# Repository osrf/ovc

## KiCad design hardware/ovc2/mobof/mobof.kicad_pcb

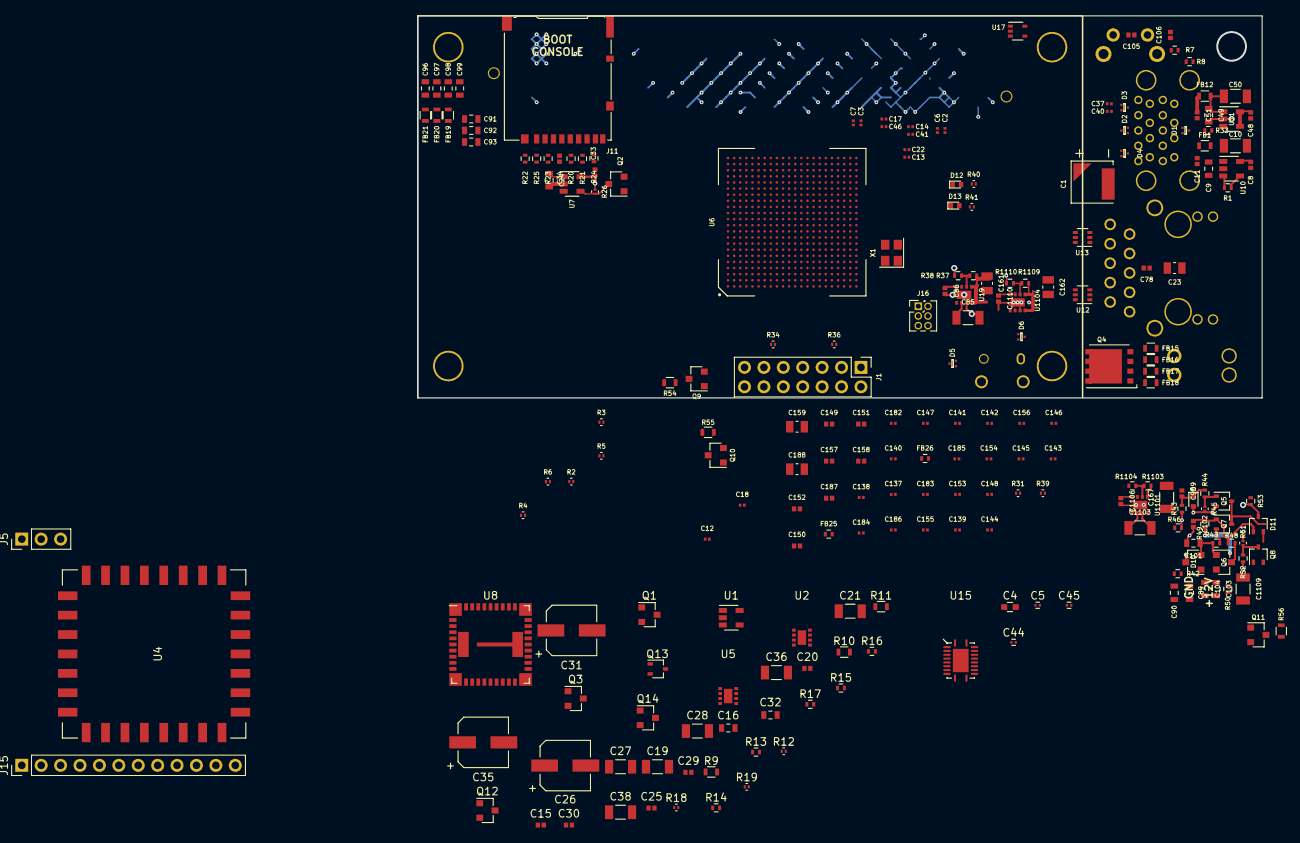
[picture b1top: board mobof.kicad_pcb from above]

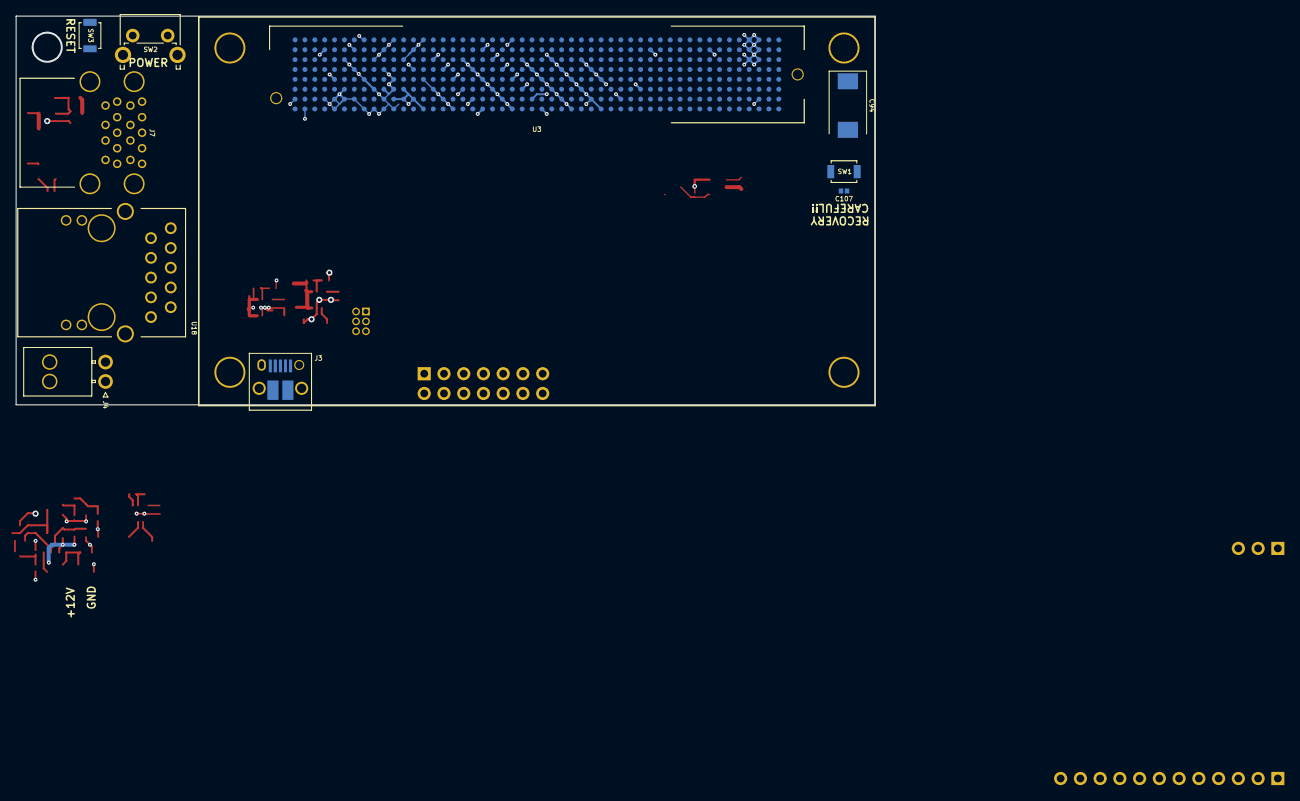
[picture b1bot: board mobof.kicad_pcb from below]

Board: 6 copper layers, 110.5 x 50.0 mm, 225 parts (10 on the bottom side), 154 nets.

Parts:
C1: 80m; SEIKO_XH414HG_IV01E
C2, C3, C6, C7, C12, C13, C14, C17, C22, C37, C40, C41, C46, C146, C147, C154, C155, C183, C184: 100n; C_0201_0603Metric
C4: 10u; C_0603
C5, C44, C45: 100n; C_0201
C8, C11, C30, C34, C48, C51: 100n; C_0402_1005Metric
C9, C24, C49, C91, C92, C93, C96, C97, C98, C99, C103, C104: 10u; C_0603_1608Metric
C10, C28, C36, C38, C50, C167: 100u; C_1206_3216Metric
C15, C33, C102, C150, C158, C187: 1u; C_0402_1005Metric
C16, C101: 2u2; C_0603_1608Metric
C18, C143: 10n; C_0201_0603Metric
C19, C21, C27, C85, C1103, C1109: 47u; C_1206_3216Metric
C20, C25, C86, C1106, C1110: 4n7; C_0402_1005Metric
C23: 100p; C_0805_2012Metric
C26: 100u; CP_Elec_6.3x7.7
C29, C78: 10n; C_0402_1005Metric
C31, C35: 220u; CP_Elec_6.3x5.8
C32: 22u; C_0603_1608Metric
C89: 100n; C_0603_1608Metric
C90: 4u7; C_0603_1608Metric
C94: 100u; CP_EIA-7343-43_Kemet-X
C95, C149, C157: 470n; C_0402_1005Metric
C105, C106, C107: 1n; C_0402_1005Metric
C137, C138, C139, C140, C141, C142, C153, C182: 22n; C_0201_0603Metric
C144, C145: 47n; C_0201_0603Metric
C148, C156, C185: 220n; C_0201_0603Metric
C151, C152: 4u7; C_0402_1005Metric
C159, C188: 100u; C_0805_2012Metric
C161, C162: 22u; C_0805_2012Metric
C186: 470n; C_0201_0603Metric
D1, D2, D3, D4, D5, D6: TPD2EUSB30A; TPD2EUSB30x
D9: RB521S30T1G; D_SOD-523
D10: BAT54ALT1G; SOT-23
D11: BAT54CW-7-F; SOT-323_SC-70
D12: LED_Red; LED_0402
D13: LED_Green; LED_0402
FB1, FB12: 220; R_0603
FB15, FB16, FB17, FB18, FB19, FB20, FB21: 30; R_0603
FB25, FB26: 60; R_0402
J1: FPGA DEBUG; Pin_Header_Straight_2x07_Pitch2.54mm
J3: USB_OTG; USB_Micro-B_10103594-0001LF
J4: POWER; Molex_NanoFit_1x02x2.50mm_Angled
J5: IMU DEBUG; Pin_Header_Straight_1x03_Pitch2.54mm
J7: USB3_A_STACKED; MOLEX_0484060003
J11: Micro_SD_Card_Det_Hirose_DM3AT; Hirose_DM3AT-SF-PEJM5
J15: IMU; Pin_Header_Straight_1x12_Pitch2.54mm
J16: FPGA CONFIG; Pin_Header_Straight_2x03_Pitch1.27mm
Q1, Q3, Q9, Q10, Q11, Q12: NTR4003NT1G; SOT-23
Q2, Q14: DMN2041L; SOT-23
Q4: AON6407; TDSON-8-1
Q5, Q7, Q8, Q13: NTS4001NT1G; SOT-323_SC-70
Q6: MMBT4403; SOT-23
R1, R33, R42, R44, R46, R47, R48: 10k; R_0402
R2, R3, R4, R5, R6, R12: 10k; R_0201
R7, R8: 681; R_0402
R9, R10, R11, R56: 47; R_0603
R13: 124k; R_0402
R14, R15, R17, R38, R43, R49, R52, R53, R1104, R1110: 100k; R_0402
R16: 28k7; R_0402
R18: 1M; R_0201
R19: 2k87; R_0201
R20: 0; R_0402
R21, R22, R23, R24, R25: 10; R_0402
R26, R45, R51: 47k; R_0201
R31, R39: 2k; R_0201
R34, R36: 1k; R_0201
R37, R1109: 523k; R_0402
R40, R41: 330; R_0201
R50: 10M; R_0402
R54, R55: 100; R_0603
R1103: 316k; R_0402
SW1: recovery; SW_SPST_B3U-1000P
SW2: SW_Push; SW_Tactile_SPST_Angled_PTS645Vx58-2LFS
SW3: SW_Push; SW_SPST_B3U-1000P
U1: TPS70933DBV; SOT-23-5
U2, U5, U19, U1101, U1104: TPS82130
U3: Jetson; JETSON_TX
U4: VN-100
U6: 10CX220; INTEL_U484
U7: NCP380LSN10AAT1G; SOT-23-5
U8: LMZ31707; TI_RVQ_42
U10, U11: TPS2069C; SOT-23-5
U12, U13: SP3002-04JTG; SOT-363_SC-70-6
U15: TXB0108RGY; TI_VQFN_20_RGY
U17: 74LVC1G34; SOT-353_SC-70-5
U18: ARJ11C-MBSAS-A-BA-7MU2
X1: ASEMB-100MHz; Oscillator_SMD_Abracon_ASE-4pin_3.2x2.5mm

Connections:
0V9: C35.1, C36.1, C38.1, C137.1, C138.1, C139.1, C140.1, C141.1, C142.1, C143.1, C144.1, C145.1, C146.1, C147.1, C148.1, C149.1, C150.1, C151.1, C152.1, R10.1, U6.J12, U6.J13, U6.K6, U6.K12, U6.K14, U6.K15, U6.K16, U6.L6, U6.L7, U6.L8, U6.L9, U6.L11, U6.L12, U6.L13, U6.L14, U6.L16, U6.M6, U6.M10, U6.M14, U6.M15, U6.M16, U6.N6, U6.N7, U6.N8, U6.N10, U6.N11, U6.N12, U6.N13, U6.N15, U6.N16, U6.P7, U6.P8, U6.P9, U6.P10, U6.P12, U6.P13, U6.P14, U6.P15, U6.R6, U6.R7, U6.R11, U6.R12, U6.R15, U6.R16, U8.27, U8.34, U8.35, U8.36, U8.37, U8.38, U8.41
1V03: C32.1, FB26.2, R11.1, R16.1, U5.4, U5.5
3V3_ALWAYS_ON: C16.1, R12.1, R15.2, U1.5
+1V8: C12.1, C18.1, C28.1, C31.1, C44.1, FB25.2, J1.9, R2.1, R3.1, R4.1, R5.1, R6.1, R9.1, R13.1, R34.1, U2.4, U2.5, U6.C9, U6.D11, U6.D16, U6.F10, U6.F15, U6.H14, U6.J1, U6.J8, U6.J14, U6.K2, U6.K3, U6.R9, U6.R14, U6.T8, U6.T9, U6.T15, U6.U9, U6.U12, U6.V9, U6.V14, U6.W6, U6.Y8, U15.2, U15.10, U17.5, X1.1, X1.4
+3V3: C4.1, C5.1, C33.1, C45.1, C167.1, J15.1, R26.1, R56.1, R1103.1, U4.10, U7.5, U15.19, U18.12, U18.13, U1101.4, U1101.5
+5V: C8.1, C162.1, R55.1, R1109.1, U10.5, U1104.4, U1104.5
+12V: C15.1, C19.1, C21.1, C26.1, C27.1, C30.1, C85.1, C91.1, C92.1, C93.1, C95.1, C1103.1, C1109.1, D10.3, FB19.2, FB20.2, FB21.2, Q4.5, R46.1, R51.1, U1.1, U2.2, U5.2, U8.1, U8.3, U8.11, U8.12, U8.39, U8.40, U19.2, U1101.2, U1104.2
/fpga_config/TCK: J1.3, R36.1, U6.P5
/fpga_config/TDI: J1.7, R4.2, U6.M4
/fpga_config/TDO: J1.1, U6.M5
/fpga_config/TMS: J1.5, R6.2, U6.L3
/fpga_io/CLK100: U6.AA6, X1.3
/fpga_io/PCIE_RST_1V8: U6.AB8, U17.4
/fpga_pcie/GXB_TX_L0+: C22.2, U6.AA22
/fpga_pcie/GXB_TX_L0-: C13.2, U6.AA21
/fpga_pcie/GXB_TX_L1+: C14.2, U6.W22
/fpga_pcie/GXB_TX_L1-: C41.2, U6.W21
/fpga_pcie/REFCLK+: C17.2, U6.M20
/fpga_pcie/REFCLK-: C46.2, U6.M19
/fpga_power/RREF_BL: R31.1, U6.AB19
/fpga_power/RREF_TL: R39.1, U6.A22
/fpga_power/VCCA: C182.1, C183.1, C184.1, C185.1, C186.1, C187.1, C188.1, FB25.1, U6.L19, U6.M11, U6.M13
/fpga_power/VCC_GXBL: C153.1, C154.1, C155.1, C156.1, C157.1, C158.1, C159.1, FB26.1, U6.J19, U6.J20, U6.N19, U6.N20
/imu/CS_3V3: J15.12, U4.23, U15.12
/imu/MISO_3V3: J15.9, U4.19, U15.15
/imu/MOSI_3V3: J15.8, U4.17, U15.16
/imu/NRST_3V3: J15.10, U4.21, U15.14
/imu/RX2: J5.1, U4.6
/imu/SCK_3V3: J15.7, U4.16, U15.17
/imu/SYNC_IN_3V3: J15.11, U4.22, U15.13
/imu/SYNC_OUT_3V3: J15.4, U4.9, U15.18
/imu/TARE_3V3: J15.3, U4.7, U15.20
/imu/TX2: J5.2, U4.5
/jetson_enet/GBE_MDI0+: U3.E48, U12.1, U18.1
/jetson_enet/GBE_MDI0-: U3.E49, U12.3, U18.2
/jetson_enet/GBE_MDI1+: U3.F47, U12.6, U18.3
/jetson_enet/GBE_MDI1-: U3.F48, U12.4, U18.4
/jetson_enet/GBE_MDI2+: U3.G48, U13.1, U18.7
/jetson_enet/GBE_MDI2-: U3.G49, U13.3, U18.8
/jetson_enet/GBE_MDI3+: U3.H47, U13.6, U18.9
/jetson_enet/GBE_MDI3-: U3.H48, U13.4, U18.10
/jetson_enet/LINK_1G: R8.1, U18.11
/jetson_enet/LINK_ACT: R7.1, U18.14
/jetson_pcie/PEX0_TX+: C6.2, U3.E44
/jetson_pcie/PEX0_TX-: C2.2, U3.E45
/jetson_pcie/PEX1_TX+: C7.2, U3.D42
/jetson_pcie/PEX1_TX-: C3.2, U3.D43
/jetson_power/POWER_BTN: C105.1, SW2.1, U3.B50
/jetson_power/RESET_IN: C106.1, SW3.1, U3.A47
/jetson_power/VDD_RTC: C1.1, U3.A50
/jetson_sdcard/SDCARD_CD: J11.9, U3.F17
/jetson_sdcard/SDCARD_CLK: J11.5, R20.1
/jetson_sdcard/SDCARD_CMD: J11.3, R23.1
/jetson_sdcard/SDCARD_D0: J11.7, R21.1
/jetson_sdcard/SDCARD_D1: J11.8, R24.1
/jetson_sdcard/SDCARD_D2: J11.1, R22.1
/jetson_sdcard/SDCARD_D3: J11.2, R25.1
/jetson_sdcard/SDCARD_PWR_EN: Q2.1, U3.H16
/jetson_sdcard/SDCARD_VDD: C24.1, C34.1, J11.4, U7.1
/jetson_usb/SS1_TX+: C37.2, U3.C43
/jetson_usb/SS1_TX-: C40.2, U3.C44
/jetson_usb/USB1_D+: D1.1, J7.3, U3.A38
/jetson_usb/USB1_D-: D1.2, J7.2, U3.A39
/jetson_usb/USB1_EN: R1.1, U3.A18, U10.4
/jetson_usb/USB1_VBUS: C11.1, FB1.2, J7.1
/power/AGND: C29.2, Q14.2, R18.2, R19.2, U8.2, U8.23, U8.29
/power/DROP_DETECT: C102.1, D11.1, Q7.1, R48.2, R49.1
/power/PG_GRP1: R15.1, U2.1, U8.8
/power/PH: U8.10, U8.13, U8.14, U8.15, U8.16, U8.17, U8.18, U8.19, U8.42
/power/VIN: FB15.2, FB16.2, FB17.2, FB18.2, J4.1
/power/~PWR_EN: D11.2, Q8.3, R51.2, R52.1
/power/~PWR_EN_GRP1: Q13.3, Q14.1, R12.2
DISCHARGE: D11.3, Q1.1, Q3.1, Q9.1, Q10.1, Q11.1, Q12.1, R53.1
FPGA_CONFIG_DATA0: J16.3, U3.F13, U6.V7
FPGA_CONFIG_DCLK: J16.4, U3.G13, U6.T2
FPGA_CONF_DONE: J16.1, R3.2, U6.M1
FPGA_NCONFIG: J16.5, R2.2, U6.U5
FPGA_NSTATUS: J16.2, R5.2, U6.L1
GND: C1.2, C4.2, C5.2, C8.2, C9.2, C10.2, C11.2, C12.2, C15.2, C16.2, C18.2, C19.2, C20.2, C21.2, C23.2, C24.2, C25.2, C26.2, C27.2, C28.2, C30.2, C31.2, C32.2, C33.2, C34.2, C35.2, C36.2, C38.2, C44.2, C45.2, C48.2, C49.2, C50.2, C51.2, C78.1, C85.2, C86.2, C89.2, C91.2, C92.2, C93.2, C94.2, C96.2, C97.2, C98.2, C99.2, C101.2, C102.2, C103.2, C104.2, C105.2, C106.2, C107.2, C137.2, C138.2, C139.2, C140.2, C141.2, C142.2, C143.2, C144.2, C145.2, C146.2, C147.2, C148.2, C149.2, C150.2, C151.2, C152.2, C153.2, C154.2, C155.2, C156.2, C157.2, C158.2, C159.2, C161.2, C162.2, C167.2, C182.2, C183.2, C184.2, C185.2, C186.2, C187.2, C188.2, C1103.2, C1106.2, C1109.2, C1110.2, D1.3, D2.3, D3.3, D4.3, D5.3, D6.3, D9.2, D12.1, D13.1, J1.13, J3.5, J3.6, J4.2, J5.3, J7.4, J7.7, J7.13, J7.16, J11.6, J11.10, J11.11, J15.2, J16.6, Q1.2, Q2.2, Q3.2, Q5.2, Q7.2, Q8.2, Q9.2, Q10.2, Q11.2, Q12.2, Q13.2, R14.2, R17.2, R31.2, R36.2, R38.2, R39.2, R42.2, R43.2, R45.2, R46.2, R47.2, R49.2, R50.2, R52.2, R53.2, R1104.2, R1110.2, SW1.2, SW2.2, SW3.2, U1.2, U2.3, U2.9, U3.A3, U3.A4, U3.A28, U3.A37, U3.A40, U3.A43, U3.B3, U3.B4, U3.B14, U3.B31, U3.B38, U3.B41, U3.B44, U3.B47, U3.C3, U3.C4, U3.C21, U3.C24, U3.C27, U3.C30, U3.C33, U3.C36, U3.C39, U3.C42, U3.C45, U3.D20, U3.D23, U3.D26, U3.D29, U3.D32, U3.D35, U3.D38, U3.D41, U3.D44, U3.E19, U3.E22, U3.E25, U3.E28, U3.E31, U3.E34, U3.E37, U3.E40, U3.E43, U3.E46, U3.F10, U3.F15, U3.F21, U3.F24, U3.F27, U3.F30, U3.F33, U3.F36, U3.F39, U3.F40, U3.F41, U3.F42, U3.F45, U3.F49, U3.G3, U3.G17, U3.G20, U3.G23, U3.G26, U3.G29, U3.G32, U3.G35, U3.G38, U3.G39, U3.G40, U3.G41, U3.G44, U3.G45, U3.G46, U3.G47, U3.G50, U3.H19, U3.H22, U3.H25, U3.H28, U3.H31, U3.H34, U3.H37, U3.H40, U3.H41, U3.H42, U3.H43, U3.H46, U3.H49, U4.1, U4.2, U4.3, U4.4, U4.18, U4.28, U4.30, U5.3, U5.9, U6.A4, U6.A9, U6.A14, U6.A18, U6.A19, U6.A20, U6.A21, U6.AA5, U6.AA10, U6.AA15, U6.AA18, U6.AA19, U6.AA20, U6.AB2, U6.AB7, U6.AB12, U6.AB20, U6.AB21, U6.AB22, U6.B2, U6.B7, U6.B12, U6.B17, U6.B18, U6.B19, U6.B20, U6.B21, U6.B22, U6.C4, U6.C14, U6.C20, U6.D1, U6.D4, U6.D5, U6.D6, U6.D18, U6.D20, U6.D21, U6.D22, U6.E3, U6.E4, U6.E5, U6.E6, U6.E8, U6.E13, U6.E20, U6.E21, U6.E22, U6.F3, U6.F4, U6.F5, U6.F7, U6.F12, U6.F20, U6.F21, U6.F22, U6.G2, U6.G3, U6.G7, U6.G9, U6.G10, U6.G12, U6.G17, U6.G20, U6.H2, U6.H4, U6.H9, U6.H10, U6.H18, U6.H19, U6.H20, U6.H21, U6.H22, U6.J6, U6.J9, U6.J10, U6.J11, U6.J15, U6.J16, U6.J18, U6.J21, U6.J22, U6.K8, U6.K9, U6.K10, U6.K11, U6.K13, U6.K18, U6.K19, U6.K20, U6.K21, U6.K22, U6.L5, U6.L10, U6.L15, U6.L18, U6.L20, U6.M2, U6.M3, U6.M7, U6.M12, U6.M18, U6.M21, U6.M22, U6.N3, U6.N4, U6.N5, U6.N9, U6.N14, U6.N18, U6.N21, U6.N22, U6.P1, U6.P3, U6.P6, U6.P11, U6.P16, U6.P18, U6.P19, U6.P20, U6.P21, U6.P22, U6.R3, U6.R5, U6.R8, U6.R13, U6.R20, U6.T3, U6.T5, U6.T7, U6.T10, U6.T11, U6.T13, U6.T20, U6.T21, U6.T22, U6.U2, U6.U4, U6.U7, U6.U17, U6.U20, U6.V4, U6.V20, U6.V21, U6.V22, U6.W1, U6.W9, U6.W11, U6.W16, U6.W18, U6.W19, U6.W20, U6.Y3, U6.Y13, U6.Y18, U6.Y21, U6.Y22, U7.2, U8.20, U8.21, U8.31, U8.32, U8.33, U10.2, U11.2, U12.2, U13.2, U15.11, U15.21, U17.3, U19.3, U19.9, U1101.3, U1101.9, U1104.3, U1104.9, X1.2
IMU_RX1: J15.6, U4.13
IMU_TX1: J15.5, U4.12
JETSON_CARRIER_PWR_ON: Q8.1, Q13.1, U3.A48, U5.1, U19.1, U1101.1, U1104.1
JETSON_PWR_BAD: Q5.3, Q7.3, U3.B8
JETSON_RESET_OUT: U2.7, U3.A46
JETSON_VDD_MOD: C94.1, C96.1, C97.1, C98.1, C99.1, FB19.1, FB20.1, FB21.1, U3.A1, U3.A2, U3.B1, U3.B2, U3.C1, U3.C2
unnamed: C9.1, C10.1, FB1.1, U10.1
unnamed: C20.1, U2.8
unnamed: C23.1, U18.SHLD
unnamed: C25.1, U5.8
unnamed: C29.1, U8.28
unnamed: C49.1, C50.1, FB12.1, U11.1
unnamed: C78.2, U18.5, U18.6
unnamed: C86.1, U19.8
unnamed: C89.1, C90.1, FB15.1, FB16.1, FB17.1, FB18.1, Q4.1, Q4.2, Q4.3
unnamed: C90.2, Q4.4, R42.1
unnamed: C95.2, D9.1, R43.1, R44.1
unnamed: C101.1, D10.2, Q6.1, R47.1
unnamed: C103.1, C104.1, D10.1, Q6.2, R50.1
unnamed: C107.1, SW1.1, U3.E1
unnamed: C1106.1, U1101.8
unnamed: C1110.1, U1104.8
unnamed: D12.2, R40.1
unnamed: D13.2, R41.1
unnamed: Q1.3, R9.2
unnamed: Q2.3, R26.2, U7.4
unnamed: Q3.3, R10.2
unnamed: Q5.1, R44.2, R45.1
unnamed: Q6.3, R48.1
unnamed: Q9.3, R54.2
unnamed: Q10.3, R55.2
unnamed: Q11.3, R56.2
unnamed: Q12.3, R11.2
unnamed: Q14.3, U8.30
unnamed: R1.2, U10.3
unnamed: R7.2, U3.E47
unnamed: R8.2, U3.F46
unnamed: R13.2, R14.1, U2.6
unnamed: R16.2, R17.1, U5.6
unnamed: R18.1, U8.22
unnamed: R19.1, U8.26
unnamed: R20.2, U3.G18
unnamed: R21.2, U3.H18
unnamed: R22.2, U3.F19
unnamed: R23.2, U3.G19
unnamed: R24.2, U3.H17
unnamed: R25.2, U3.F18
unnamed: R33.2, U11.3
unnamed: R34.2, U6.L4
unnamed: R37.2, R38.1, U19.6
unnamed: R1103.2, R1104.1, U1101.6
unnamed: R1109.2, R1110.1, U1104.6
PCIE_LANE0_RX+: C22.1, U3.H44
PCIE_LANE0_RX-: C13.1, U3.H45
PCIE_LANE0_TX+: C6.1, U6.Y20
PCIE_LANE0_TX-: C2.1, U6.Y19
PCIE_LANE1_RX+: C14.1, U3.G42
PCIE_LANE1_RX-: C41.1, U3.G43
PCIE_LANE1_TX+: C7.1, U6.U22
PCIE_LANE1_TX-: C3.1, U6.U21
PCIE_REFCLK+: C17.1, U3.A44
PCIE_REFCLK-: C46.1, U3.A45
PCIE_RST_3V3: U3.C49, U17.2
USB0_D+: D5.2, J3.3, U3.B39
USB0_D-: D5.1, J3.2, U3.B40
USB0_ID: D6.2, J3.4, U3.A36
USB0_VBUS: J3.1, U3.B37
USB1_SSRX+: D4.1, J7.15, U3.F43
USB1_SSRX-: D4.2, J7.14, U3.F44
USB1_SSTX+: C37.1, D3.1, J7.18
USB1_SSTX-: C40.1, D3.2, J7.17
USB2_5V: C48.1, C161.1, R33.1, R37.1, R54.1, U11.4, U11.5, U19.4, U19.5
USB2_5V_LIM: C51.1, FB12.2, J7.10
USB2_D+: D2.1, J7.12, U3.B42
USB2_D-: D2.2, J7.11, U3.B43

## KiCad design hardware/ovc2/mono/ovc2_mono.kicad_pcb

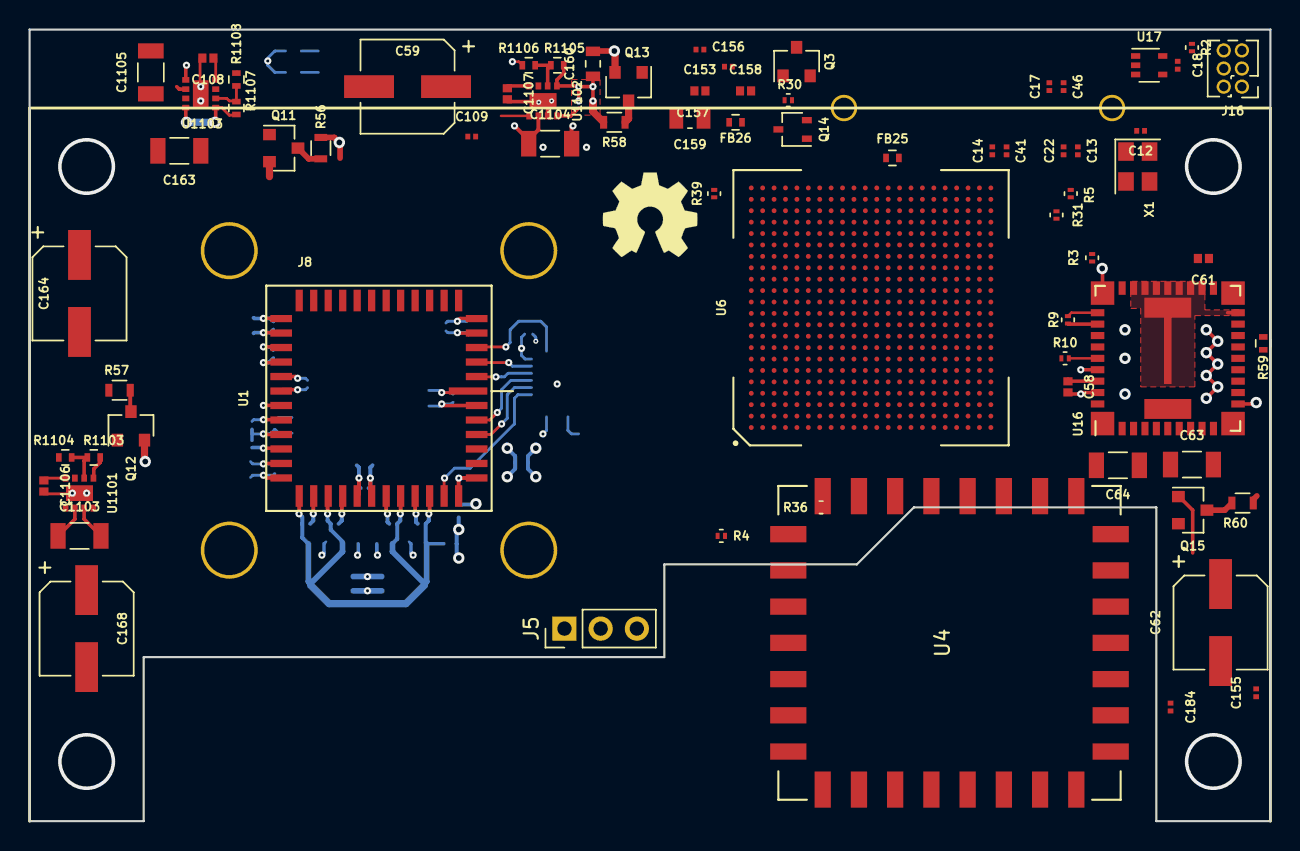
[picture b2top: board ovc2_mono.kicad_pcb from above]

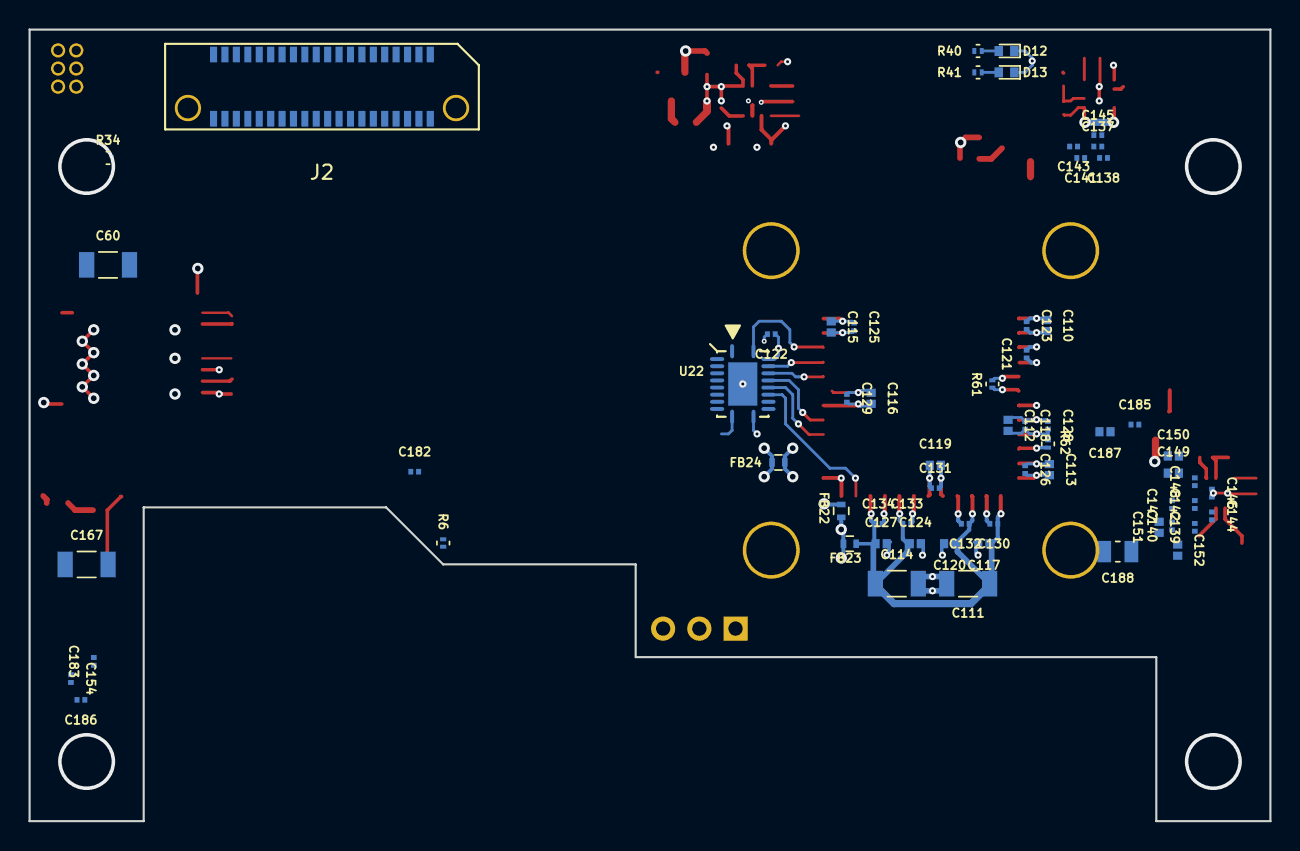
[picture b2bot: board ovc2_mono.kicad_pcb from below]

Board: 6 copper layers, 87.0 x 55.5 mm, 137 parts (63 on the bottom side), 76 nets.

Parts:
C12, C13, C14, C17, C22, C41, C46, C109, C121, C122, C123, C125, C126, C128, C129, C131, C146, C147, C154, C155, C183, C184: 100n; C_0201_0603Metric
C18, C118, C143: 10n; C_0201_0603Metric
C58: 10n; C_0402_1005Metric
C59: 100u; CP_Elec_6.3x7.7
C60, C1103, C1104, C1105: 47u; C_1206_3216Metric
C61: 100n; C_0402_1005Metric
C62, C164, C168: 220u; CP_Elec_6.3x5.8
C63, C64, C111, C114, C163, C167: 100u; C_1206_3216Metric
C108, C1106, C1107: 4n7; C_0402_1005Metric
C110, C112, C113, C115: 10u; C_0402_1005Metric
C116, C117, C119, C120, C124, C127, C151, C152: 4u7; C_0402_1005Metric
C130, C132, C133, C134: 1u; C_0201_0603Metric
C137, C138, C139, C140, C141, C142, C153, C182: 22n; C_0201_0603Metric
C144, C145: 47n; C_0201_0603Metric
C148, C156, C185: 220n; C_0201_0603Metric
C149, C157: 470n; C_0402_1005Metric
C150, C158, C187: 1u; C_0402_1005Metric
C159, C188: 100u; C_0805_2012Metric
C160: 22u; C_0603_1608Metric
C186: 470n; C_0201_0603Metric
D12: LED_Red; LED_0402
D13: LED_Green; LED_0402
FB22, FB23, FB24: 220; R_0402
FB25, FB26: 60; R_0402
J2: Conn_02x20_Odd_Even; SAMTEC_ERF8-020
J5: IMU DEBUG; Pin_Header_Straight_1x03_Pitch2.54mm
J8: LENS_HOLDER; M12_PYTHON1300_M3Mounting
J16: FPGA CONFIG; Pin_Header_Straight_2x03_Pitch1.27mm
Q3: DMN2041L; SOT-23
Q11, Q12, Q13, Q15: NTR4003NT1G; SOT-23
Q14: NTS4001NT1G; SOT-323_SC-70
R2, R3, R4, R5, R6, R30: 10k; R_0201
R9: 1M; R_0201
R10: 2k87; R_0201
R31, R39: 2k; R_0201
R34, R36: 1k; R_0201
R40, R41: 330; R_0201
R56, R57, R58, R60: 47; R_0603
R59, R1104, R1106, R1108: 100k; R_0402
R61: 100; R_0201
R62: 47k; R_0201
R1103: 316k; R_0402
R1105: 28k7; R_0402
R1107: 124k; R_0402
U1: NOIP1SN1300A-QDI; LCC101.6P1422X1422X165-48
U4: VN-100
U6: 10CX220; INTEL_U484
U16: LMZ31707; TI_RVQ_42
U17: 74LVC1G34; SOT-353_SC-70-5
U22: TXB0108RGY; TI_VQFN_20_RGY
U1101, U1102, U1103: TPS82130
X1: ASEMB-100MHz; Oscillator_SMD_Abracon_ASE-4pin_3.2x2.5mm
Z1: Logo_Open_Hardware_Small; OSHW-Symbol_6.7x6mm_SilkScreen

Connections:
0V9: C62.1, C63.1, C64.1, C137.1, C138.1, C139.1, C140.1, C141.1, C142.1, C143.1, C144.1, C145.1, C146.1, C147.1, C148.1, C149.1, C150.1, C151.1, C152.1, R60.1, U6.J12, U6.J13, U6.K6, U6.K12, U6.K14, U6.K15, U6.K16, U6.L6, U6.L7, U6.L8, U6.L9, U6.L11, U6.L12, U6.L13, U6.L14, U6.L16, U6.M6, U6.M10, U6.M14, U6.M15, U6.M16, U6.N6, U6.N7, U6.N8, U6.N10, U6.N11, U6.N12, U6.N13, U6.N15, U6.N16, U6.P7, U6.P8, U6.P9, U6.P10, U6.P12, U6.P13, U6.P14, U6.P15, U6.R6, U6.R7, U6.R11, U6.R12, U6.R15, U6.R16, U16.27, U16.34, U16.35, U16.36, U16.37, U16.38, U16.41
1V03: C160.1, FB26.2, R58.1, R1105.1, U1102.4, U1102.5
2V5_MCU: R30.1, R59.2
+1V8: C12.1, C18.1, C109.1, C163.1, C164.1, FB24.2, FB25.2, R2.1, R3.1, R4.1, R5.1, R6.1, R34.1, R57.1, R1107.1, U6.C9, U6.D11, U6.D16, U6.F10, U6.F15, U6.H14, U6.J1, U6.J8, U6.J14, U6.K2, U6.K3, U6.R9, U6.R14, U6.T8, U6.T9, U6.T15, U6.U9, U6.U12, U6.V9, U6.V14, U6.W6, U6.Y8, U17.5, U22.2, U22.10, U1103.4, U1103.5, X1.1, X1.4
+3V3: C122.1, C167.1, C168.1, FB22.2, FB23.2, R56.1, R1103.1, U4.10, U22.19, U1101.4, U1101.5
+12V: C59.1, C60.1, C61.1, C1103.1, C1104.1, C1105.1, U16.1, U16.3, U16.11, U16.12, U16.39, U16.40, U1101.2, U1102.2, U1103.2
/fpga_config/TCK: R36.1, U6.P5
/fpga_config/TDI: R4.2, U6.M4
/fpga_config/TMS: R6.2, U6.L3
/fpga_io/CLK100: U6.AA6, X1.3
/fpga_io/PCIE_RST_1V8: U6.AB8, U17.4
/fpga_pcie/GXB_TX_L0+: C22.2, U6.AA22
/fpga_pcie/GXB_TX_L0-: C13.2, U6.AA21
/fpga_pcie/GXB_TX_L1+: C14.2, U6.W22
/fpga_pcie/GXB_TX_L1-: C41.2, U6.W21
/fpga_pcie/REFCLK+: C17.2, U6.M20
/fpga_pcie/REFCLK-: C46.2, U6.M19
/fpga_power/RREF_BL: R31.1, U6.AB19
/fpga_power/RREF_TL: R39.1, U6.A22
/fpga_power/VCCA: C182.1, C183.1, C184.1, C185.1, C186.1, C187.1, C188.1, FB25.1, U6.L19, U6.M11, U6.M13
/fpga_power/VCC_GXBL: C153.1, C154.1, C155.1, C156.1, C157.1, C158.1, C159.1, FB26.1, U6.J19, U6.J20, U6.N19, U6.N20
/imagers/CAM1_1V8: C112.1, C115.1, C118.1, C121.1, C125.1, C128.1, FB24.1, U1.6, U1.22, U1.26
/imagers/CAM1_3V3: C110.1, C113.1, C116.1, C119.1, C123.1, C126.1, C129.1, C131.1, FB22.1, U1.1, U1.19, U1.29, U1.36
/imagers/CAM1_CS_3V3: U1.47, U22.16
/imagers/CAM1_MISO_3V3: U1.3, U22.18
/imagers/CAM1_MOSI_3V3: U1.2, U22.17
/imagers/CAM1_RST_3V3: U1.46, U22.15
/imagers/CAM1_SCK_3V3: U1.4, U22.20
/imagers/CAM1_TRG_3V3: U1.41, U22.14
/imagers/CAM1_VDDPIX: C111.1, C114.1, C117.1, C120.1, C124.1, C127.1, C130.1, C132.1, C133.1, C134.1, FB23.1, U1.31, U1.33, U1.38, U1.40
/imu/RX2: J5.1, U4.6
/imu/TX2: J5.2, U4.5
/power/AGND: C58.2, Q3.2, R9.2, R10.2, U16.2, U16.23, U16.29
/power/DISCHARGE: Q11.1, Q12.1, Q13.1, Q15.1
/power/PG_GRP1: R59.1, U16.8, U1101.1, U1103.1
/power/PH: U16.10, U16.13, U16.14, U16.15, U16.16, U16.17, U16.18, U16.19, U16.42
/power/~PWR_EN_GRP1: Q3.1, Q14.3, R30.2
CAM1_CLKIN+: R61.2, U1.24
CAM1_CLKIN-: R61.1, U1.23
FPGA_CONFIG_DATA0: J16.3, U6.V7
FPGA_CONFIG_DCLK: J16.4, U6.T2
FPGA_CONF_DONE: J16.1, R3.2, U6.M1
FPGA_NCONFIG: J16.5, R2.2, U6.U5
FPGA_NSTATUS: J16.2, R5.2, U6.L1
GND: C12.2, C18.2, C59.2, C60.2, C61.2, C62.2, C63.2, C64.2, C108.2, C109.2, C110.2, C111.2, C112.2, C113.2, C114.2, C115.2, C116.2, C117.2, C118.2, C119.2, C120.2, C121.2, C122.2, C123.2, C124.2, C125.2, C126.2, C127.2, C128.2, C129.2, C130.2, C131.2, C132.2, C133.2, C134.2, C137.2, C138.2, C139.2, C140.2, C141.2, C142.2, C143.2, C144.2, C145.2, C146.2, C147.2, C148.2, C149.2, C150.2, C151.2, C152.2, C153.2, C154.2, C155.2, C156.2, C157.2, C158.2, C159.2, C160.2, C163.2, C164.2, C167.2, C168.2, C182.2, C183.2, C184.2, C185.2, C186.2, C187.2, C188.2, C1103.2, C1104.2, C1105.2, C1106.2, C1107.2, D12.1, D13.1, J2.16, J2.22, J2.28, J2.31, J2.34, J2.37, J2.39, J2.40, J5.3, J16.6, Q11.2, Q12.2, Q13.2, Q14.2, Q15.2, R31.2, R36.2, R39.2, R62.2, R1104.2, R1106.2, R1108.2, U1.5, U1.20, U1.21, U1.25, U1.27, U1.30, U1.32, U1.34, U1.35, U1.37, U1.39, U1.42, U1.43, U1.48, U4.1, U4.2, U4.3, U4.4, U4.18, U4.28, U4.30, U6.A4, U6.A9, U6.A14, U6.A18, U6.A19, U6.A20, U6.A21, U6.AA5, U6.AA10, U6.AA15, U6.AA18, U6.AA19, U6.AA20, U6.AB2, U6.AB7, U6.AB12, U6.AB20, U6.AB21, U6.AB22, U6.B2, U6.B7, U6.B12, U6.B17, U6.B18, U6.B19, U6.B20, U6.B21, U6.B22, U6.C4, U6.C14, U6.C20, U6.D1, U6.D4, U6.D5, U6.D6, U6.D18, U6.D20, U6.D21, U6.D22, U6.E3, U6.E4, U6.E5, U6.E6, U6.E8, U6.E13, U6.E20, U6.E21, U6.E22, U6.F3, U6.F4, U6.F5, U6.F7, U6.F12, U6.F20, U6.F21, U6.F22, U6.G2, U6.G3, U6.G7, U6.G9, U6.G10, U6.G12, U6.G17, U6.G20, U6.H2, U6.H4, U6.H9, U6.H10, U6.H18, U6.H19, U6.H20, U6.H21, U6.H22, U6.J6, U6.J9, U6.J10, U6.J11, U6.J15, U6.J16, U6.J18, U6.J21, U6.J22, U6.K8, U6.K9, U6.K10, U6.K11, U6.K13, U6.K18, U6.K19, U6.K20, U6.K21, U6.K22, U6.L5, U6.L10, U6.L15, U6.L18, U6.L20, U6.M2, U6.M3, U6.M7, U6.M12, U6.M18, U6.M21, U6.M22, U6.N3, U6.N4, U6.N5, U6.N9, U6.N14, U6.N18, U6.N21, U6.N22, U6.P1, U6.P3, U6.P6, U6.P11, U6.P16, U6.P18, U6.P19, U6.P20, U6.P21, U6.P22, U6.R3, U6.R5, U6.R8, U6.R13, U6.R20, U6.T3, U6.T5, U6.T7, U6.T10, U6.T11, U6.T13, U6.T20, U6.T21, U6.T22, U6.U2, U6.U4, U6.U7, U6.U17, U6.U20, U6.V4, U6.V20, U6.V21, U6.V22, U6.W1, U6.W9, U6.W11, U6.W16, U6.W18, U6.W19, U6.W20, U6.Y3, U6.Y13, U6.Y18, U6.Y21, U6.Y22, U16.20, U16.21, U16.31, U16.32, U16.33, U17.3, U22.11, U22.21, U1101.3, U1101.9, U1102.3, U1102.9, U1103.3, U1103.9, X1.2
JETSON_CARRIER_PWR_ON: J2.25, Q14.1, U1102.1
JETSON_RESET_OUT: J2.27, U1103.7
unnamed: C58.1, U16.28
unnamed: C108.1, U1103.8
unnamed: C1106.1, U1101.8
unnamed: C1107.1, U1102.8
unnamed: D12.2, R40.1
unnamed: D13.2, R41.1
unnamed: Q3.3, U16.30
unnamed: Q11.3, R56.2
unnamed: Q12.3, R57.2
unnamed: Q13.3, R58.2
unnamed: Q15.3, R60.2
unnamed: R9.1, U16.22
unnamed: R10.1, U16.26
unnamed: R34.2, U6.L4
unnamed: R62.1, U1.28
unnamed: R1103.2, R1104.1, U1101.6
unnamed: R1105.2, R1106.1, U1102.6
unnamed: R1107.2, R1108.1, U1103.6
PCIE_LANE0_RX+: J2.30, U6.Y20
PCIE_LANE0_RX-: J2.32, U6.Y19
PCIE_LANE0_TX+: C22.1, J2.36
PCIE_LANE0_TX-: C13.1, J2.38
PCIE_LANE1_RX+: J2.18, U6.U22
PCIE_LANE1_RX-: J2.20, U6.U21
PCIE_LANE1_TX+: C14.1, J2.24
PCIE_LANE1_TX-: C41.1, J2.26
PCIE_REFCLK+: C17.1, J2.33
PCIE_REFCLK-: C46.1, J2.35
PCIE_RST_3V3: J2.29, U17.2
